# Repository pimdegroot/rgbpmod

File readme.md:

# RGB Pmod
 ## Introducion
 In this repo you can find the design files and a code example for the rgb matrix pmod I designed. It is based on a 1x1mm RGB led and the GN1640 LED driver.

 The leds used are: https://lcsc.com/product-detail/Light-Emitting-Diodes-LED_Foshan-NationStar-Optoelectronics-FC-B1010RGBT-HG_C158099.html

And the driver is: https://lcsc.com/product-detail/LED-Drivers_GN-GN1640_C265478.html

Note that the TM1640 is pin compatible and an english datasheet can be found for that chip.

When replicating this project it is highly recommended to order a stencil and use solder paste to solder the LEDs

## Usage and Support
Feel free to use the design and code in this repo for your own project. Please credit this repo, or @mifune on twitter if you do.

This is a hobby project that I shared because there has been some interest in it. I will not offer it for sale (though I won't stop you from doing so). Please let me know if there is a file missing in the repo, other than that I won't offer support. I'm already working on the next project.

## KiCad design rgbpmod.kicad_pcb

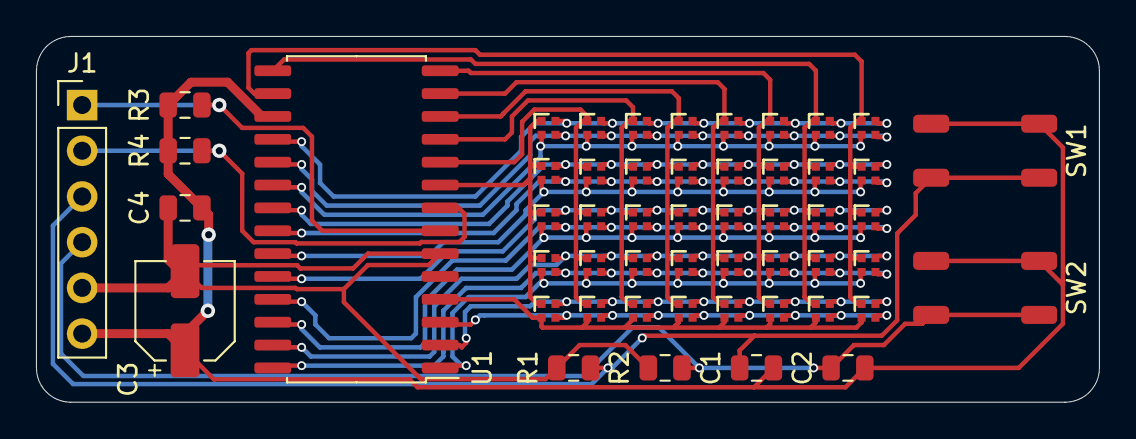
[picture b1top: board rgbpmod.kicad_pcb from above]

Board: 2 copper layers, 59.1 x 20.3 mm, 52 parts (0 on the bottom side), 29 nets.

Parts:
C1, C2: 100n; C_0805_2012Metric
C3: 100uf; CP_Elec_5x5.4
C4: 100nf; C_0805_2012Metric
D1, D2, D3, D4, D5, D6, D7, D8, D9, D10, D11, D12, D13, D14, D15, D16, D17, D18, D19, D20, D21, D22, D23, D24, D25, D26, D27, D28, D29, D30, D31, D32, D33, D34, D35, D36, D37, D38, D39, D40: LED_ARGB; 0404_RGB_LED
J1: Conn_01x06; PinHeader_1x06_P2.54mm_Vertical
R1, R2, R3, R4: 10k; R_0805_2012Metric
SW1, SW2: SW_Push; SW
U1: GM1640; SOIC-28W_7.5x17.9mm_P1.27mm

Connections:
BTN1: C1.1, J1.3, R1.2, SW1.2
BTN2: C2.1, J1.4, R2.2, SW2.2
DIN: J1.1, R3.2, U1.7
GND: C3.2, C4.1, J1.5, R1.1, R2.1, U1.6
GRID1: D1.2, D6.2, D11.2, D16.2, D21.2, D26.2, D31.2, D36.2, U1.18
GRID2: D1.3, D6.3, D11.3, D16.3, D21.3, D26.3, D31.3, D36.3, U1.19
GRID3: D1.4, D6.4, D11.4, D16.4, D21.4, D26.4, D31.4, D36.4, U1.20
GRID4: D2.2, D7.2, D12.2, D17.2, D22.2, D27.2, D32.2, D37.2, U1.21
GRID5: D2.3, D7.3, D12.3, D17.3, D22.3, D27.3, D32.3, D37.3, U1.22
GRID6: D2.4, D7.4, D12.4, D17.4, D22.4, D27.4, D32.4, D37.4, U1.23
GRID7: D3.2, D8.2, D13.2, D18.2, D23.2, D28.2, D33.2, D38.2, U1.24
GRID8: D3.3, D8.3, D13.3, D18.3, D23.3, D28.3, D33.3, D38.3, U1.25
GRID9: D3.4, D8.4, D13.4, D18.4, D23.4, D28.4, D33.4, D38.4, U1.26
GRID10: D4.2, D9.2, D14.2, D19.2, D24.2, D29.2, D34.2, D39.2, U1.27
GRID11: D4.3, D9.3, D14.3, D19.3, D24.3, D29.3, D34.3, D39.3, U1.28
GRID12: D4.4, D9.4, D14.4, D19.4, D24.4, D29.4, D34.4, D39.4, U1.1
GRID13: D5.2, D10.2, D15.2, D20.2, D25.2, D30.2, D35.2, D40.2, U1.2
GRID14: D5.3, D10.3, D15.3, D20.3, D25.3, D30.3, D35.3, D40.3, U1.3
GRID15: D5.4, D10.4, D15.4, D20.4, D25.4, D30.4, D35.4, D40.4, U1.4
SCLK: J1.2, R4.2, U1.8
SEG1: D1.1, D2.1, D3.1, D4.1, D5.1, U1.9
SEG2: D6.1, D7.1, D8.1, D9.1, D10.1, U1.10
SEG3: D11.1, D12.1, D13.1, D14.1, D15.1, U1.11
SEG4: D16.1, D17.1, D18.1, D19.1, D20.1, U1.12
SEG5: D21.1, D22.1, D23.1, D24.1, D25.1, U1.13
SEG6: D26.1, D27.1, D28.1, D29.1, D30.1, U1.14
SEG7: D31.1, D32.1, D33.1, D34.1, D35.1, U1.15
SEG8: D36.1, D37.1, D38.1, D39.1, D40.1, U1.16
VCC: C1.2, C2.2, C3.1, C4.2, J1.6, R3.1, R4.1, SW1.1, SW2.1, U1.17

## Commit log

2020-11-08 Initial Release
